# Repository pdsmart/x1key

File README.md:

# x1key
A PS/2 to Sharp X1 Keyboard Interface

Please see my website, https://eaw.app for more documentation and recent updates.

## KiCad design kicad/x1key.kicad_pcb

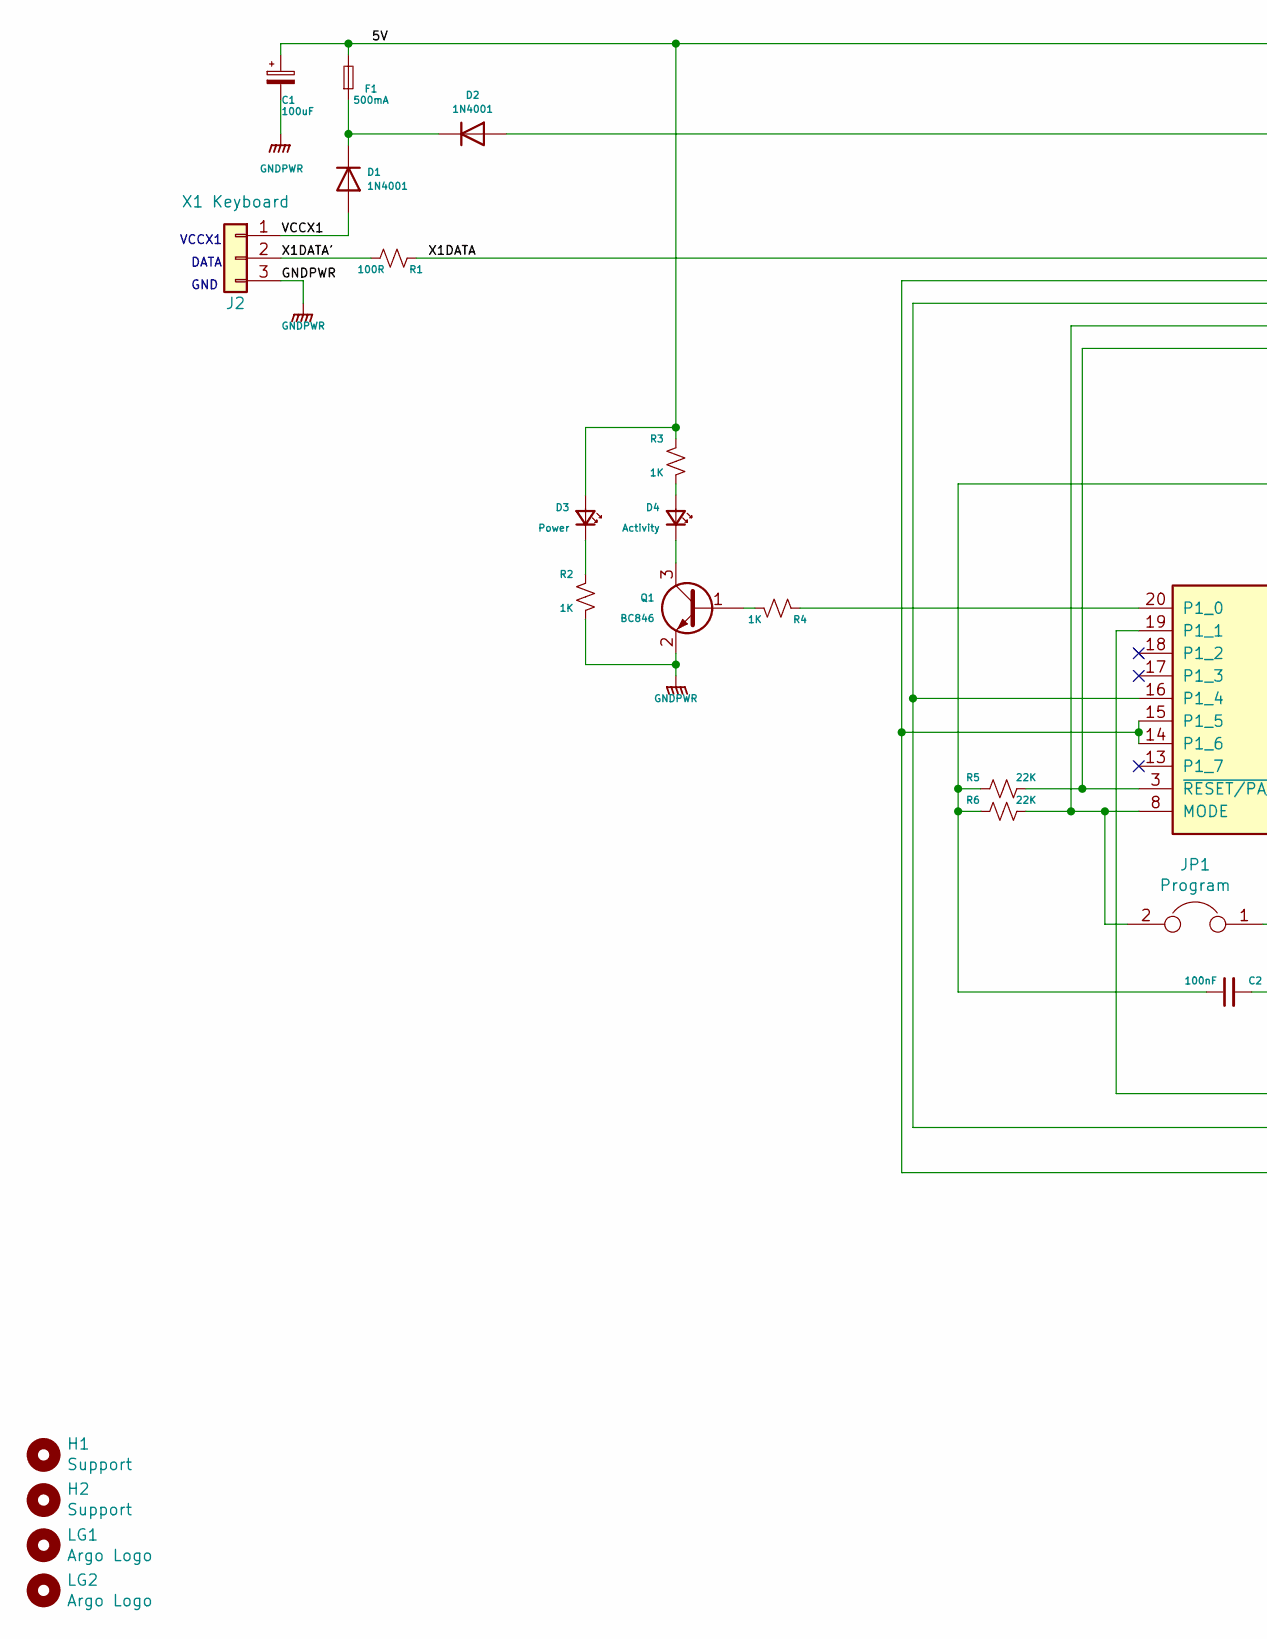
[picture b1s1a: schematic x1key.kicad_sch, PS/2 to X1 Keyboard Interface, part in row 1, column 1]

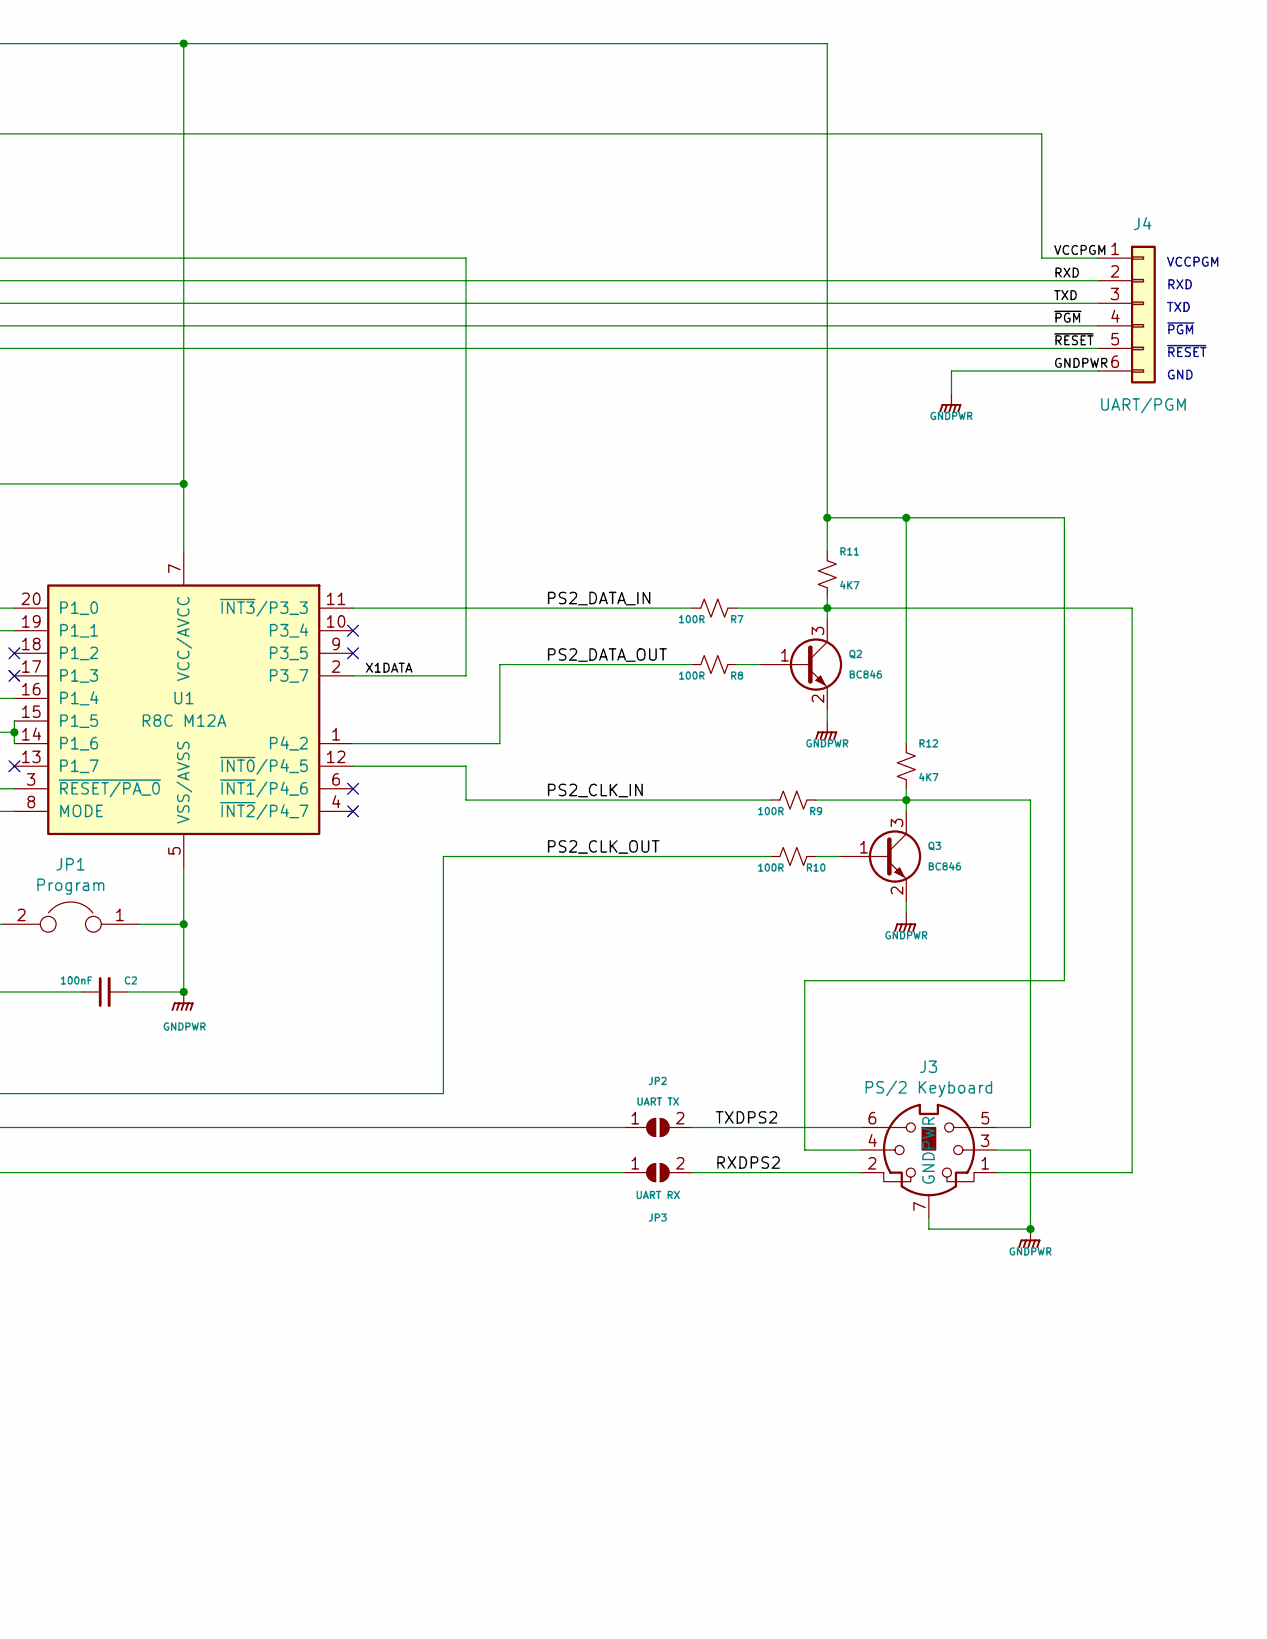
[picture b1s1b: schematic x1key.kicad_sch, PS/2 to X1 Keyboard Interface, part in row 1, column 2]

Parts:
C1: 100uF; C_1812_4532Metric
C2: 100nF; C_0805_2012Metric_Pad1.15x1.40mm_HandSolder
D1, D2: 1N4001; D_SMA
D3: Power; LED_D3.0mm_Clear
D4: Activity; LED_D3.0mm_Clear
F1: 500mA; Fuse_1812_4532Metric
H1, H2: Support; MountingHole_2.1mm
J2: X1 Keyboard; PinHeader_1x03_P2.00mm_Vertical
J3: PS/2 Keyboard; Mini_din6_ps2
J4: UART/PGM; PinHeader_1x06_P2.00mm_Vertical
JP1: Program; PinHeader_1x02_P2.00mm_Vertical
JP2: UART TX; SolderJumper-2_P1.3mm_Open_Pad1.0x1.5mm
JP3: UART RX; SolderJumper-2_P1.3mm_Open_Pad1.0x1.5mm
LG1, LG2: Argo Logo; Argo
Q1, Q2, Q3: BC846; SOT-23
R1, R7, R8, R9, R10: 100R; R_0805_2012Metric
R2, R3, R4: 1K; R_0805_2012Metric
R5, R6: 22K; R_0805_2012Metric
R11, R12: 4K7; R_0805_2012Metric
U1: R8C M12A; TSSOP-20_4.4x6.5mm_P0.65mm

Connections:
/5V: C1.1, C2.1, D3.2 (A), F1.2, J3.4, R3.1, R5.1, R6.1, R11.1, R12.1, U1.7 (VCC/AVCC)
/PS2_CLK_IN: R9.1, U1.12 (~INT0/P4_5)
/PS2_CLK_OUT: R10.1, U1.19 (P1_1)
/PS2_DATA_IN: R7.1, U1.11 (~INT3/P3_3)
/PS2_DATA_OUT: R8.1, U1.1 (P4_2)
/RXD: J4.2, JP3.1 (A), U1.14 (P1_6), U1.15 (P1_5)
/RXDPS2: J3.2, JP3.2 (B)
/TXD: J4.3, JP2.1 (A), U1.16 (P1_4)
/TXDPS2: J3.6, JP2.2 (B)
/VCCPGM: D2.2 (A), J4.1
/VCCX1: D1.2 (A), J2.1
/X1DATA: R1.2, U1.2 (P3_7)
/X1DATA': J2.2, R1.1
/~PGM: J4.4, JP1.2, R6.2, U1.8 (MODE)
/~RESET: J4.5, R5.2, U1.3 (~RESET/PA_0)
GNDPWR: C1.2, C2.2, J2.3, J3.3, J3.7 (GNDPWR), J4.6, JP1.1, Q1.2 (E), Q2.2 (E), Q3.2 (E), R2.2, U1.5 (VSS/AVSS)
unnamed: D1.1 (K), D2.1 (K), F1.1
unnamed: D3.1 (K), R2.1
unnamed: D4.1 (K), Q1.3 (C)
unnamed: D4.2 (A), R3.2
unnamed: J3.1, Q2.3 (C), R7.2, R11.2
unnamed: J3.5, Q3.3 (C), R9.2, R12.2
unnamed: Q1.1 (B), R4.2
unnamed: Q2.1 (B), R8.2
unnamed: Q3.1 (B), R10.2
unnamed: R4.1, U1.20 (P1_0)

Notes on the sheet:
~{PGM}
GND
VCCPGM
TXD
~{RESET}
RXD
VCCX1
DATA

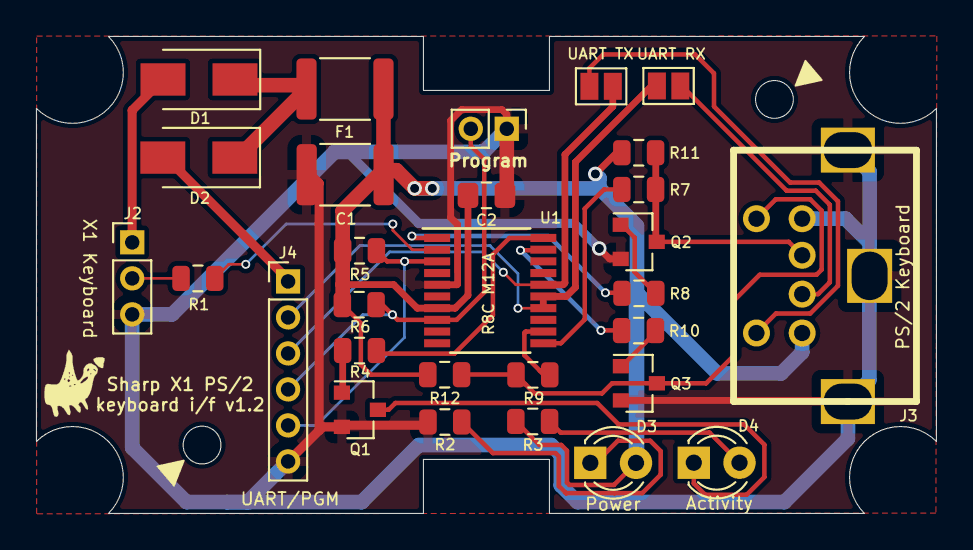
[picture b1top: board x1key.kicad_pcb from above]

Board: 2 copper layers, 50.0 x 26.5 mm, 33 parts (1 on the bottom side), 26 nets.

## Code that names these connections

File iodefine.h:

/*
    Connect a PS / 2 keyboard to SHARP X1
    Definition of I / O pins, etc.

    Created July 22, 2014

    Kyoichi Sato http://kyoutan.jpn.org/

    There is no guarantee.
    The part created by Kyoichi Sato has no restrictions on its use. You can use it freely regardless of whether it is commercial or non-commercial.
    It means that you can copy, modify, distribute, or sell it without permission.
    No need to contact.
*/

#ifndef IODEFINE_H
#define IODEFINE_H

#ifdef __cplusplus
    extern "C" {
#endif

// LED
#define LED            p1_0

// UART
#define TXD            p1_4
#define RXD            p1_5

// PS/2 Interface.
#define PS2_DATA_IN    p3_3
#define PS2_DATA_OUT   p4_2
#define PS2_CLK_IN     p4_5
#define PS2_CLK_OUT    p1_1
#define PS2DATA        p3_3
#define X1KEYOUT       p3_7

// X1 Keyboard interface.
#define X1DATA         p3_7

#define TRUE           1
#define FALSE          0
#define ON             1
#define OFF            0
#define NULL           0

#define DI() asm ("FCLR I") // Interrupt disabled
#define EI() asm ("FSET I") // Interrupt enabled

// Types missing in the Renesas C compiler headers.
typedef unsigned char uint8_t;

#ifdef __cplusplus
}
#endif
#endif // IODEFINE_H

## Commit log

2022-02-17 First push
2022-03-09 PCB and Schematic files added
2022-03-12 added git attributes
